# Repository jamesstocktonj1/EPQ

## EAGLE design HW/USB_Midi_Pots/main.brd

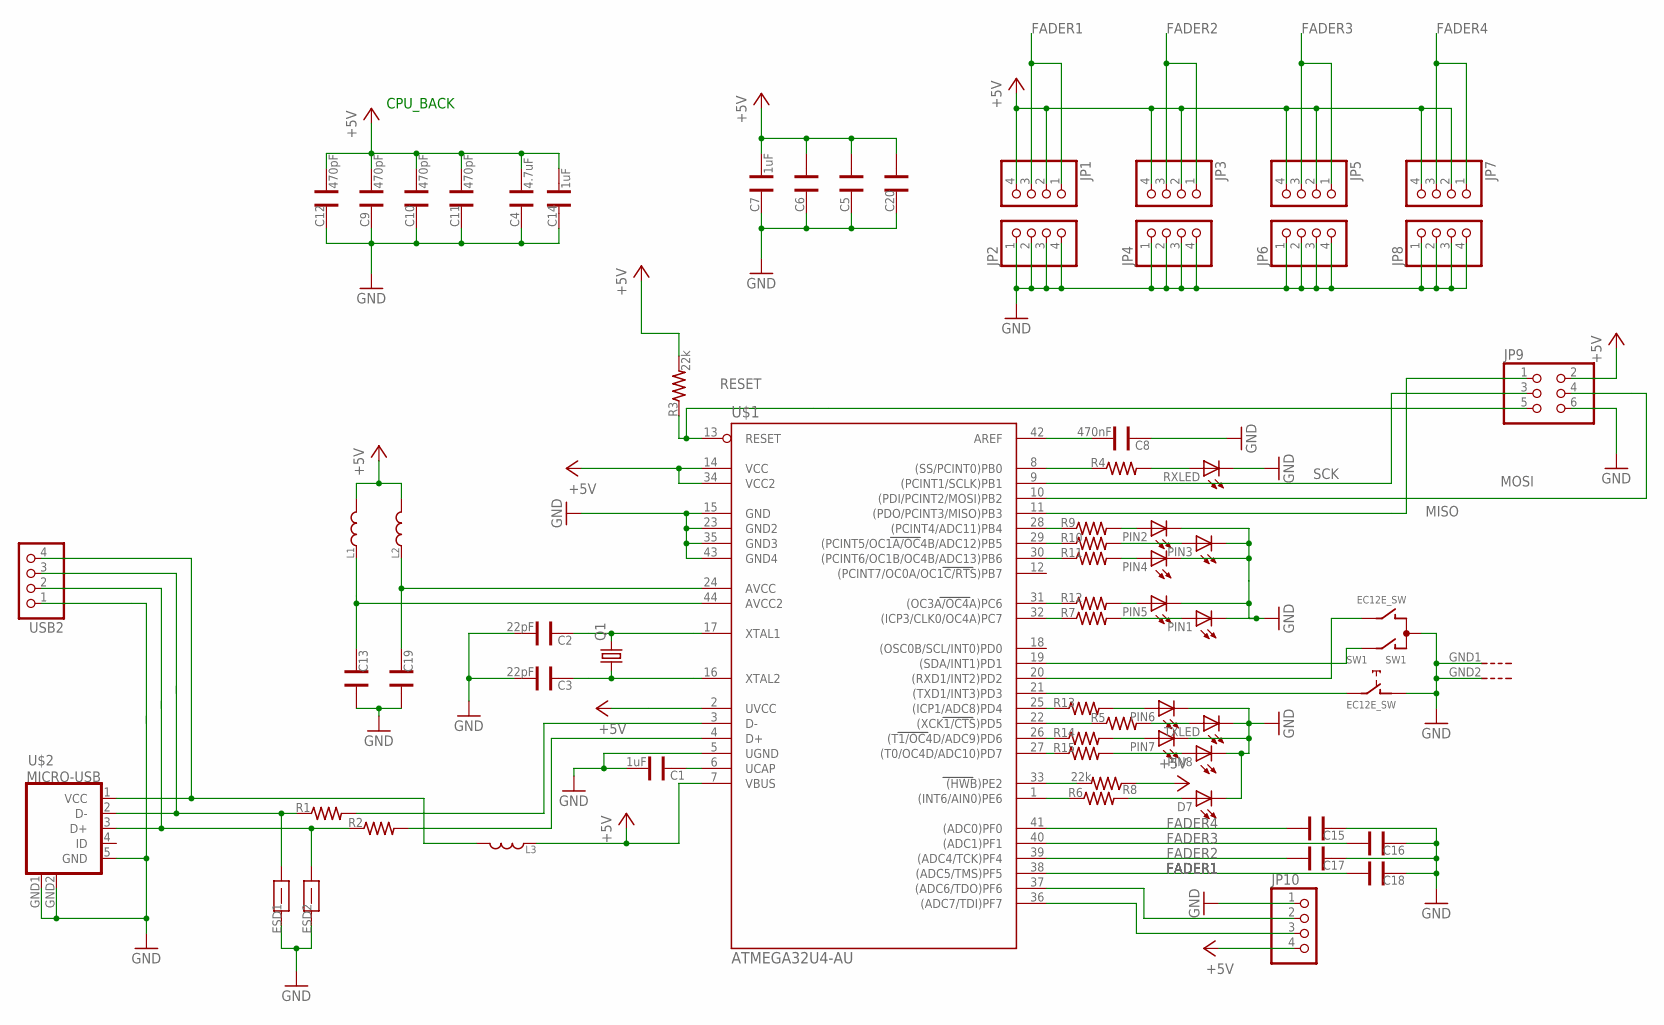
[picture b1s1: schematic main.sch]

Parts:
C1, C7, C14: 1uF; CAP-0805
C2, C3: 22pF; CAP-0603
C4: 4.7uF; CAP-0805
C5, C6, C13, C19, C20: CAP0805; CAP-0805
C8: 470nF; CAP-0603
C9, C10, C11, C12: 470pF; CAP-0603
C15, C16, C17, C18: CAP0603; CAP-0603
D7: LED0603; LED-0603
ESD1, ESD2: FB; FB-0603
JP1, JP2, JP3, JP4, JP5, JP6, JP7, JP8, JP10: PINHD-1X4; 1X04
JP9: PINHD-2X3; 2X03
L1, L2, L3: IND0603; IND-0603
PIN1, PIN2, PIN3, PIN4, PIN5, PIN6, PIN7, PIN8: LED0603; LED-0603
Q1: CRYSTALHC49S; HC49/S
R1, R2, R4, R5, R6, R7, R9, R10, R11, R12, R13, R14, R15: RES0603; RES-0603
R3, R8: 22k; RES-0603
RXLED: LED0603; LED-0603
SW1: EC12E_SW; ALPS_EC12E_SW
TXLED: LED0603; LED-0603
U$1: ATMEGA32U4-AU; TQFP44
U$2: MICRO-USB
USB2: PINHD-1X4; 1X04

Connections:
+5V: C4.1, C5.1, C6.1, C7.1, C9.1, C10.1, C11.1, C12.1, C14.1, C20.1, JP1.2, JP1.4, JP3.2, JP3.4, JP5.2, JP5.4, JP7.2, JP7.4, JP9.2, JP10.4, L1.1, L2.1, L3.2, R3.2, R8.1, U$1.2 (UVCC), U$1.7 (VBUS), U$1.14 (VCC), U$1.34 (VCC2)
FADER1: C18.1, JP1.1, JP1.3, U$1.38 ((ADC5/TMS)PF5)
FADER2: C17.1, JP3.1, JP3.3, U$1.39 ((ADC4/TCK)PF4)
FADER3: C16.1, JP5.1, JP5.3, U$1.40 ((ADC1)PF1)
FADER4: C15.1, JP7.1, JP7.3, U$1.41 ((ADC0)PF0)
GND: C1.1, C2.1, C3.1, C4.2, C5.2, C6.2, C7.2, C8.2, C9.2, C10.2, C11.2, C12.2, C13.1, C14.2, C15.2, C16.2, C17.2, C18.2, C19.1, C20.2, D7.C, ESD1.1, ESD2.1, JP2.1, JP2.2, JP2.3, JP2.4, JP4.1, JP4.2, JP4.3, JP4.4, JP6.1, JP6.2, JP6.3, JP6.4, JP8.1, JP8.2, JP8.3, JP8.4, JP9.6, JP10.1, PIN1.C, PIN2.C, PIN3.C, PIN4.C, PIN5.C, PIN6.C, PIN7.C, PIN8.C, RXLED.C, SW1.C, SW1.D (1), SW1.GND1 (G), SW1.GND2 (G), TXLED.C, U$1.5 (UGND), U$1.15 (GND), U$1.23 (GND2), U$1.35 (GND3), U$1.43 (GND4), U$2.5 (GND), U$2.GND1 (GND), U$2.GND2 (GND), USB2.1
MISO: JP9.1, U$1.11 ((PDO/PCINT3/MISO)PB3)
MOSI: JP9.4, U$1.10 ((PDI/PCINT2/MOSI)PB2)
unnamed: ESD1.2, R1.1, U$2.2 (D-), USB2.3
unnamed: ESD2.2, R2.1, U$2.3 (D+), USB2.2
unnamed: R1.2, U$1.3 (D-)
unnamed: R2.2, U$1.4 (D+)
unnamed: R8.2, U$1.33 ((HWB)PE2)
unnamed: C1.2, U$1.6 (UCAP)
unnamed: C2.2, Q1.2, U$1.17 (XTAL1)
unnamed: JP10.2, U$1.37 ((ADC6/TDO)PF6)
unnamed: R7.1, U$1.32 ((ICP3/CLK0/OC4A)PC7)
unnamed: R4.1, U$1.8 ((SS/PCINT0)PB0)
unnamed: R4.2, RXLED.A
unnamed: R5.1, U$1.22 ((XCK1/CTS)PD5)
unnamed: R5.2, TXLED.A
unnamed: C13.2, L1.2, U$1.44 (AVCC2)
unnamed: C19.2, L2.2, U$1.24 (AVCC)
unnamed: C8.1, U$1.42 (AREF)
unnamed: PIN1.A, R7.2
unnamed: PIN2.A, R9.2
unnamed: SW1.E (2), U$1.21 ((TXD1/INT3)PD3)
unnamed: SW1.B, U$1.20 ((RXD1/INT2)PD2)
unnamed: SW1.A, U$1.19 ((SDA/INT1)PD1)
unnamed: PIN5.A, R12.2
unnamed: PIN4.A, R11.2
unnamed: PIN3.A, R10.2
unnamed: JP10.3, U$1.36 ((ADC7/TDI)PF7)
unnamed: R9.1, U$1.28 ((PCINT4/ADC11)PB4)
unnamed: R10.1, U$1.29 ((PCINT5/OC1A/OC4B/ADC12)PB5)
unnamed: R11.1, U$1.30 ((PCINT6/OC1B/OC4B/ADC13)PB6)
unnamed: R12.1, U$1.31 ((OC3A/OC4A)PC6)
unnamed: R13.1, U$1.25 ((ICP1/ADC8)PD4)
unnamed: R14.1, U$1.26 ((T1/OC4D/ADC9)PD6)
unnamed: R15.1, U$1.27 ((T0/OC4D/ADC10)PD7)
unnamed: PIN6.A, R13.2
unnamed: PIN7.A, R14.2
unnamed: PIN8.A, R15.2
unnamed: R6.1, U$1.1 ((INT6/AIN0)PE6)
unnamed: C3.2, Q1.1, U$1.16 (XTAL2)
unnamed: D7.A, R6.2
unnamed: L3.1, U$2.1 (VCC), USB2.4
RESET: JP9.5, R3.1, U$1.13 (RESET)
SCK: JP9.3, U$1.9 ((PCINT1/SCLK)PB1)

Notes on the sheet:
CPU_BACK

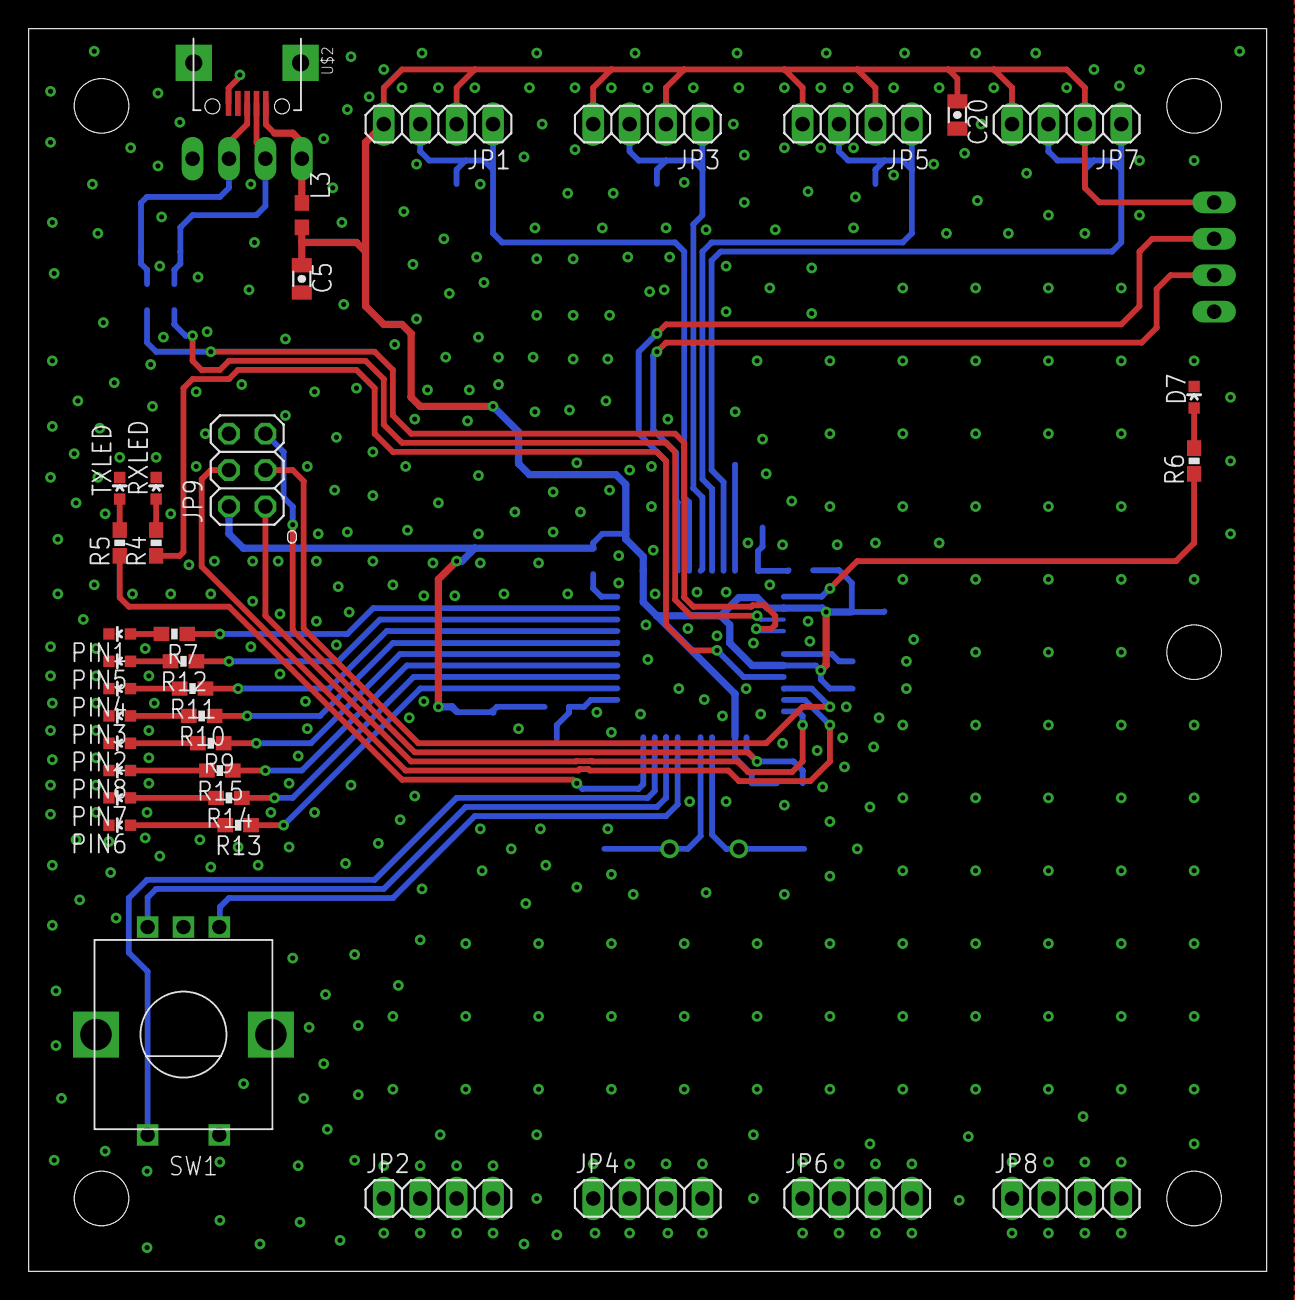
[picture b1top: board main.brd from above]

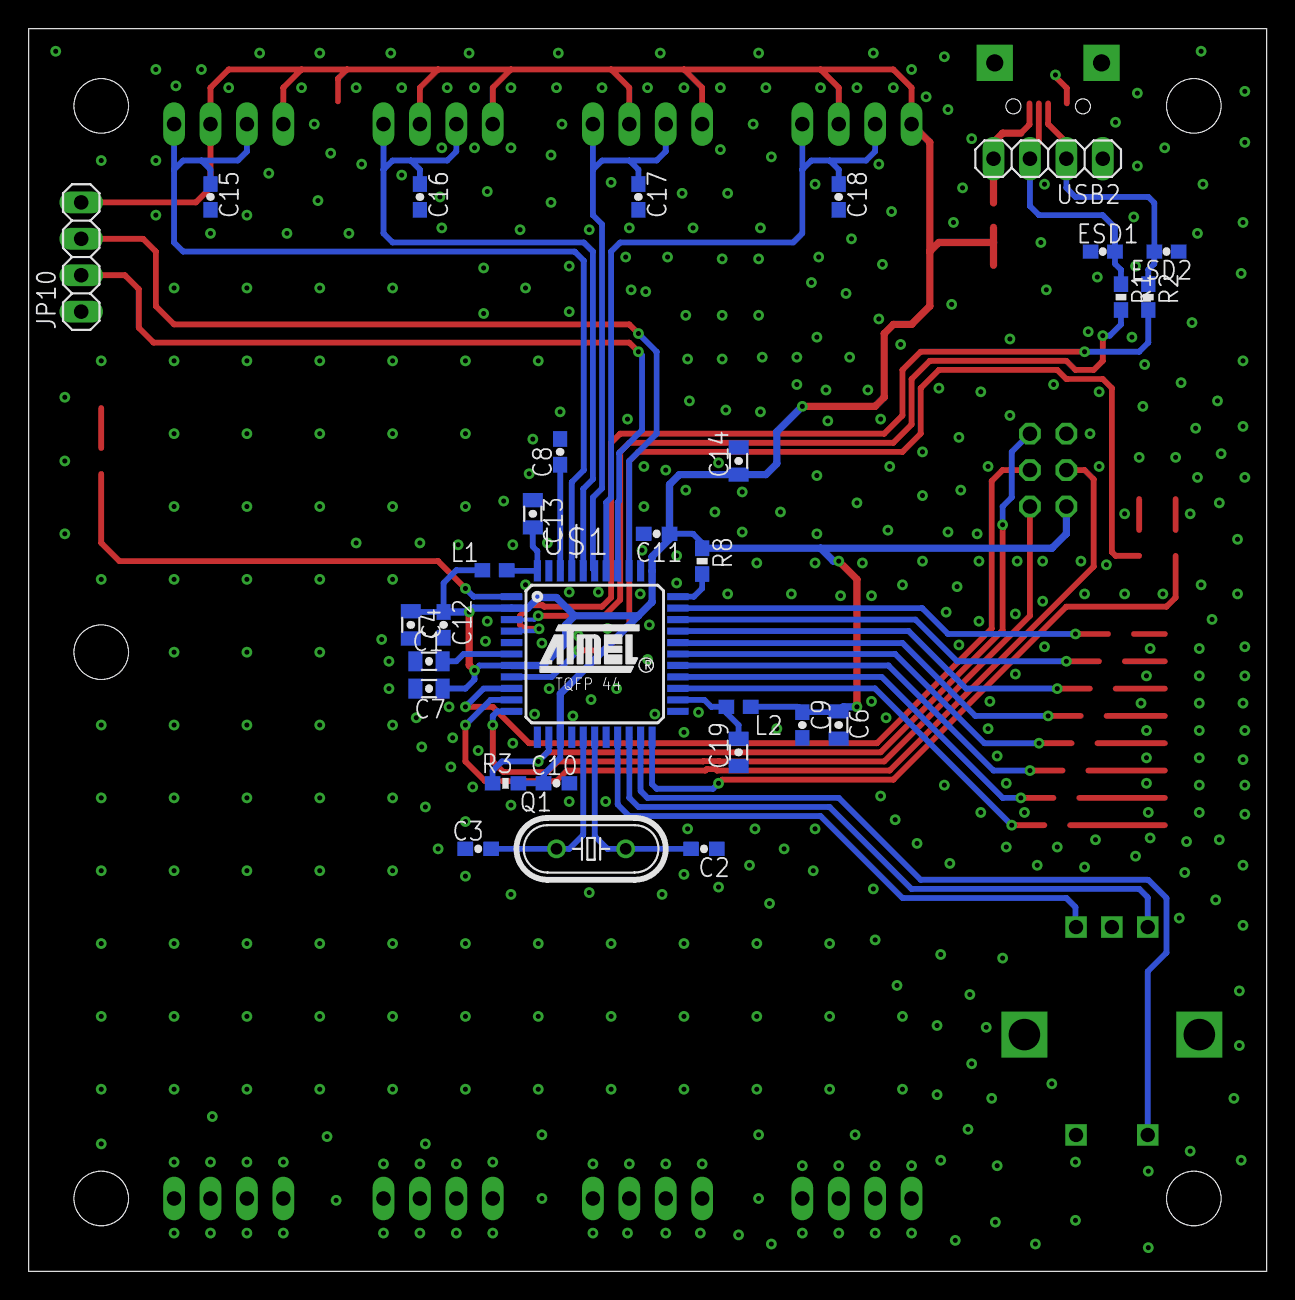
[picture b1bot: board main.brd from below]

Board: 2 copper layers, 86.3 x 86.7 mm, 66 parts (30 on the bottom side), 49 nets.

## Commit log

2018-09-22 Almost final PCB design and starting software
2018-09-22 Capture pictures of board layout
2018-09-22 Original Potentiometer software converted to a library
2018-09-22 Potentiometer library and test
2018-09-22 Name Change
2018-09-22 Midi Pots using library
2018-09-22 Assembly test code may be used to some degree
2018-09-22 HW update
2018-09-23 Sources for HW and SW
2018-09-26 Board Update
2018-10-05 Rotary Encoder Test and other Board Layouts
2018-10-06 Final Code Version 1
2019-04-21 Extra Source
